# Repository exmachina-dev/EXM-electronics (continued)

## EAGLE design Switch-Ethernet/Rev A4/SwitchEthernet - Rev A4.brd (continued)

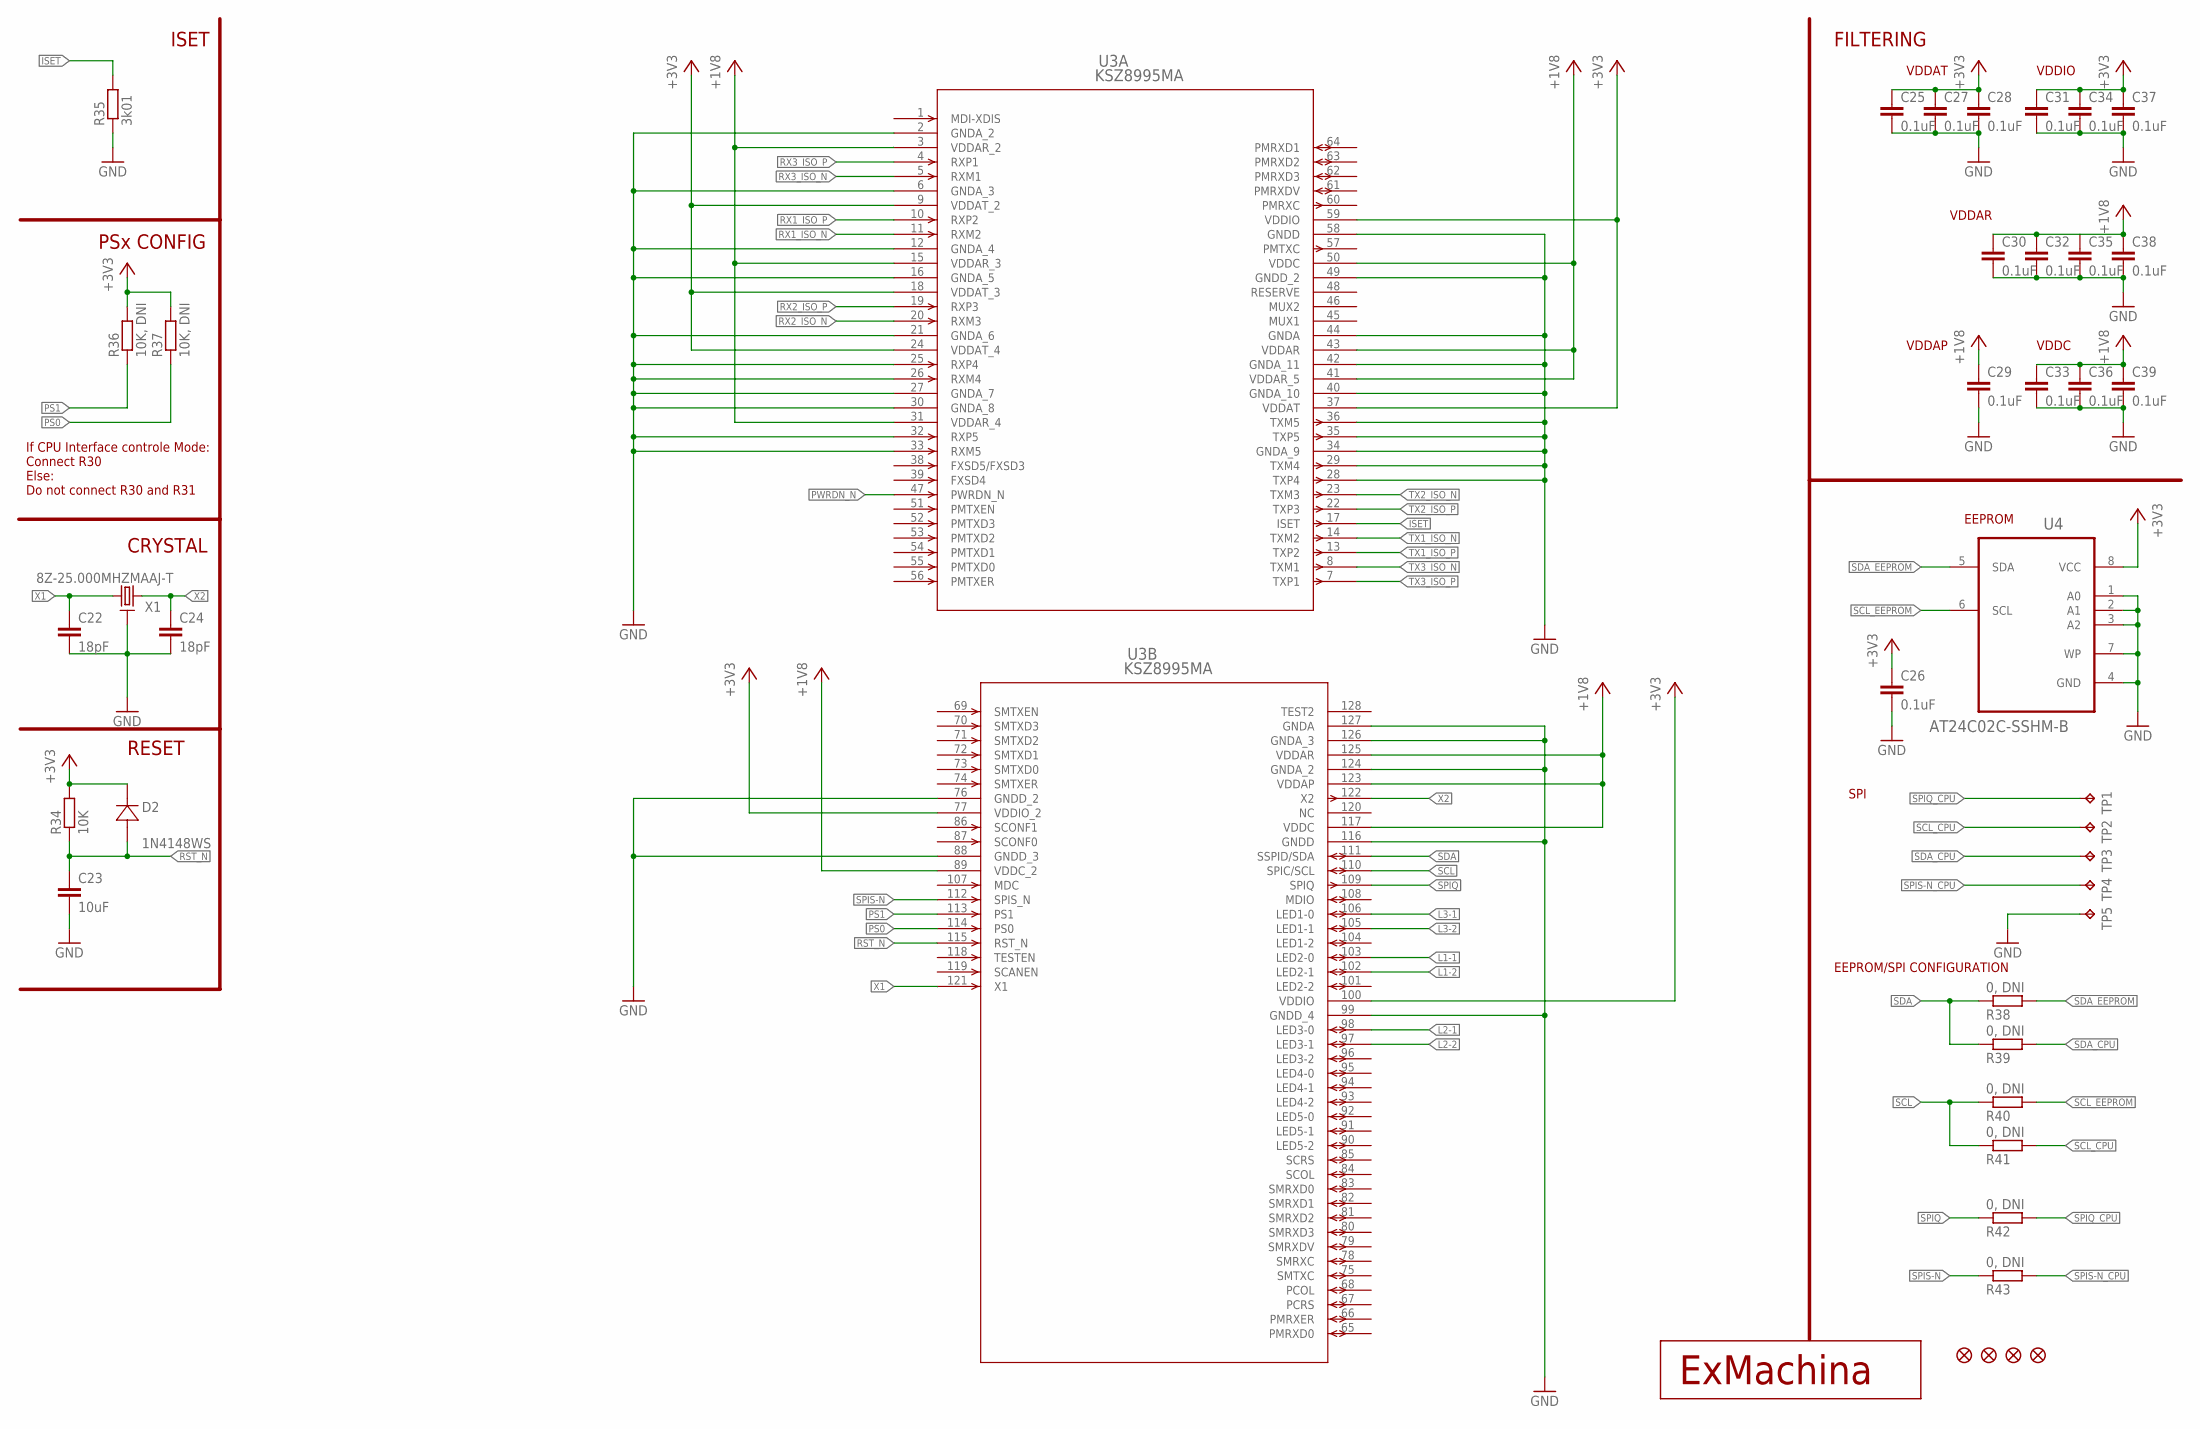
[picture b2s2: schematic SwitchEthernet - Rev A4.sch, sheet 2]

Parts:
C22, C24: 18pF; C0603; MPN MC0603N180J500CT
C23: 10uF; C0603; MPN GRM188R60J106ME47D
C25, C26, C27, C28, C29, C30, C31, C32, C33, C34, C35, C36, C37, C38, C39: 0.1uF; C0603; MPN MC0603B104K160CT
D2: 1N4148WS; SOD323-W; MPN 1N4148WS.
JP1, JP2, JP3, JP4: FIDUCIAL1X2; FIDUCIAL-1X2
R34: 10K; R0603; MPN MC0063W0603110K
R35: 3k01; R0603; MPN MC0063W060313K01
R36, R37: 10K, DNI; R0603; MPN MC0063W0603110K
R38, R39, R40, R41, R42, R43: 0, DNI; R0603; MPN MC0603WG00000T5E-TC
T3: EXMACHINA-LOGO-NAME; EXM-LOGO-BASELINE
TP1, TP2, TP3, TP4, TP5: TPB1,27; B1,27
U3: KSZ8995MA; PQFP-128_MQL
U4: AT24C02C-SSHM-B; SOIC127P600X175-8N
X1: 8Z-25.000MHZMAAJ-T; SMD2.5X2; MPN 8Z-25.000MAAJ-T

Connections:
+1V8: C29.1, C30.1, C32.1, C33.1, C35.1, C36.1, C38.1, C39.1, U3.3 (VDDAR_2), U3.15 (VDDAR_3), U3.31 (VDDAR_4), U3.41 (VDDAR_5), U3.43 (VDDAR), U3.50 (VDDC), U3.89 (VDDC_2), U3.117 (VDDC), U3.123 (VDDAP), U3.125 (VDDAR); also elsewhere on the board
+3V3: C25.1, C26.1, C27.1, C28.1, C31.1, C34.1, C37.1, D2.C (1), R34.2, R36.2, R37.2, U3.9 (VDDAT_2), U3.18 (VDDAT_3), U3.24 (VDDAT_4), U3.37 (VDDAT), U3.59 (VDDIO), U3.77 (VDDIO_2), U3.100 (VDDIO), U4.8 (VCC); also elsewhere on the board
GND: C22.2, C23.2, C24.2, C25.2, C26.2, C27.2, C28.2, C29.2, C30.2, C31.2, C32.2, C33.2, C34.2, C35.2, C36.2, C37.2, C38.2, C39.2, R35.1, TP5.TP, U3.2 (GNDA_2), U3.6 (GNDA_3), U3.12 (GNDA_4), U3.16 (GNDA_5), U3.21 (GNDA_6), U3.25 (RXP4), U3.26 (RXM4), U3.27 (GNDA_7), U3.28 (TXP4), U3.29 (TXM4), U3.30 (GNDA_8), U3.32 (RXP5), U3.33 (RXM5), U3.34 (GNDA_9), U3.35 (TXP5), U3.36 (TXM5), U3.40 (GNDA_10), U3.42 (GNDA_11), U3.44 (GNDA), U3.49 (GNDD_2), U3.58 (GNDD), U3.76 (GNDD_2), U3.88 (GNDD_3), U3.99 (GNDD_4), U3.116 (GNDD), U3.124 (GNDA_2), U3.126 (GNDA_3), U3.127 (GNDA), U4.1 (A0), U4.2 (A1), U4.3 (A2), U4.4 (GND), U4.7 (WP), X1.2, X1.4 (2); also elsewhere on the board
ISET: R35.2, U3.17 (ISET)
L1-1: U3.103 (LED2-0); also elsewhere on the board
L1-2: U3.102 (LED2-1); also elsewhere on the board
L2-1: U3.98 (LED3-0); also elsewhere on the board
L2-2: U3.97 (LED3-1); also elsewhere on the board
L3-1: U3.106 (LED1-0); also elsewhere on the board
L3-2: U3.105 (LED1-1); also elsewhere on the board
PS0: R37.1, U3.114 (PS0)
PS1: R36.1, U3.113 (PS1)
PWRDN_N: U3.47 (PWRDN_N)
RST_N: C23.1, D2.A (2), R34.1, U3.115 (RST_N)
RX1_ISO_N: U3.11 (RXM2); also elsewhere on the board
RX1_ISO_P: U3.10 (RXP2); also elsewhere on the board
RX2_ISO_N: U3.20 (RXM3); also elsewhere on the board
RX2_ISO_P: U3.19 (RXP3); also elsewhere on the board
RX3_ISO_N: U3.5 (RXM1); also elsewhere on the board
RX3_ISO_P: U3.4 (RXP1); also elsewhere on the board
SCL: R40.1, R41.1, U3.110 (SPIC/SCL)
SCL_CPU: R41.2, TP2.TP
SCL_EEPROM: R40.2, U4.6 (SCL)
SDA: R38.1, R39.1, U3.111 (SSPID/SDA)
SDA_CPU: R39.2, TP3.TP
SDA_EEPROM: R38.2, U4.5 (SDA)
SPIQ: R42.1, U3.109 (SPIQ)
SPIQ_CPU: R42.2, TP1.TP
SPIS-N: R43.1, U3.112 (SPIS_N)
SPIS-N_CPU: R43.2, TP4.TP
TX1_ISO_N: U3.14 (TXM2); also elsewhere on the board
TX1_ISO_P: U3.13 (TXP2); also elsewhere on the board
TX2_ISO_N: U3.23 (TXM3); also elsewhere on the board
TX2_ISO_P: U3.22 (TXP3); also elsewhere on the board
TX3_ISO_N: U3.8 (TXM1); also elsewhere on the board
TX3_ISO_P: U3.7 (TXP1); also elsewhere on the board
X1: C22.1, U3.121 (X1), X1.1
X2: C24.1, U3.122 (X2), X1.3

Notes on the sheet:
ISET
FILTERING
VDDIO
VDDAT
VDDAR
VDDC
VDDAP
PSx CONFIG
If CPU Interface controle Mode: Connect R30 Else: Do not connect R30 and R31
CRYSTAL
EEPROM
SPI
EEPROM/SPI CONFIGURATION
RESET

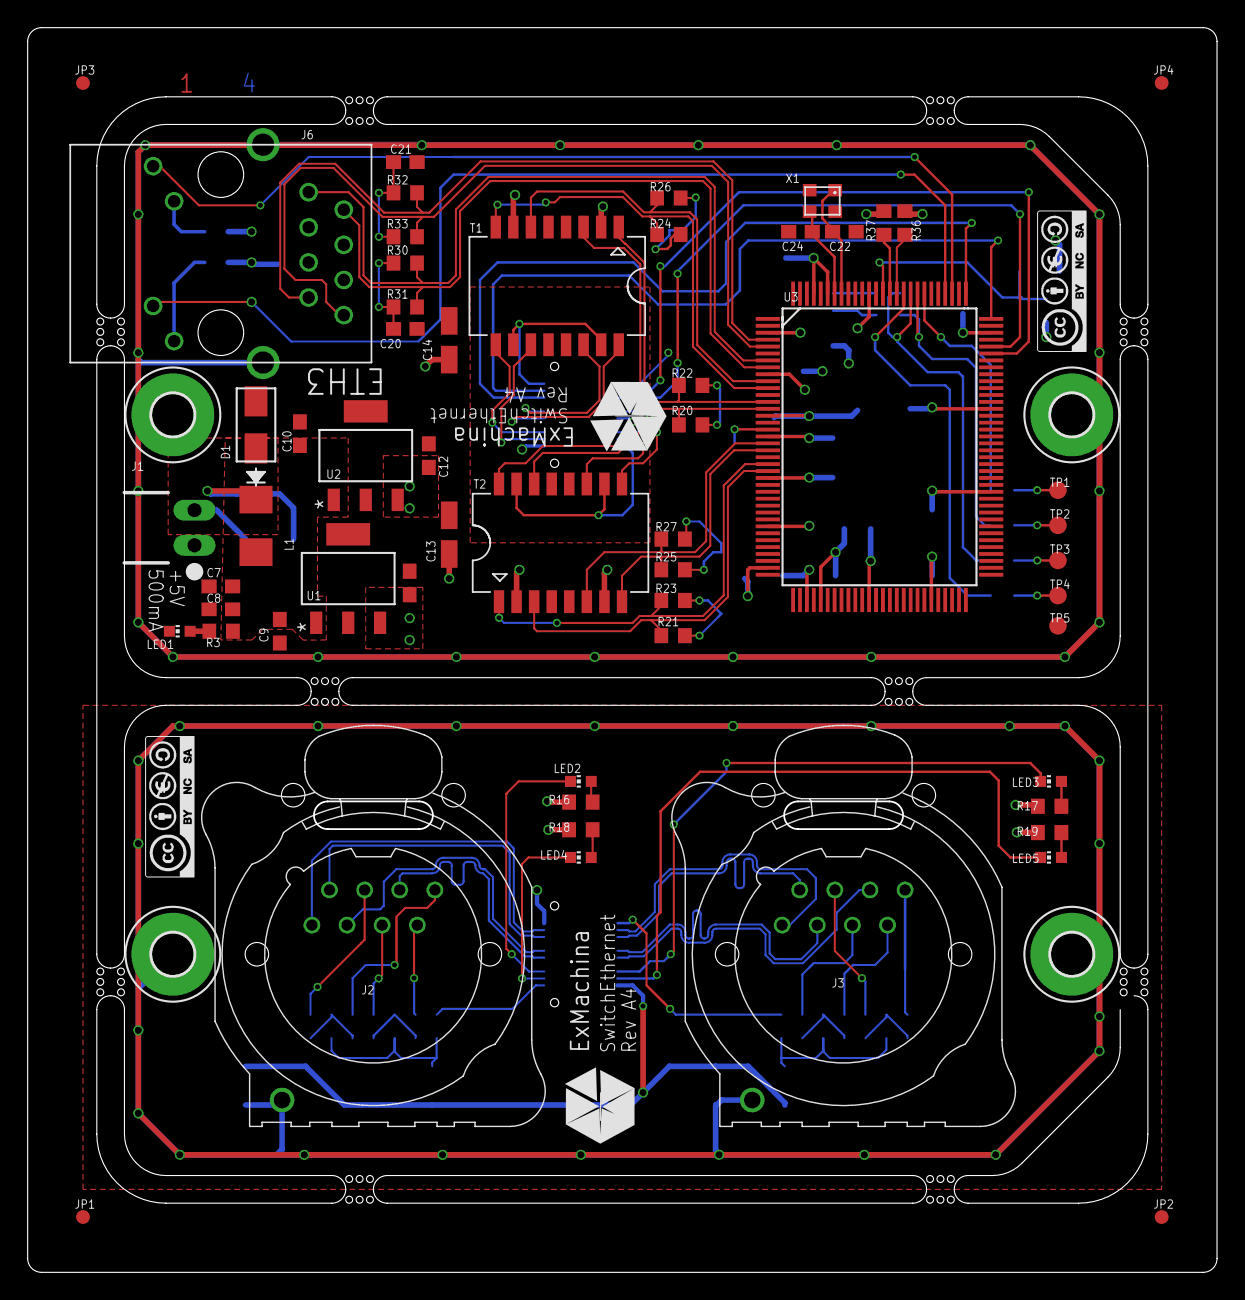
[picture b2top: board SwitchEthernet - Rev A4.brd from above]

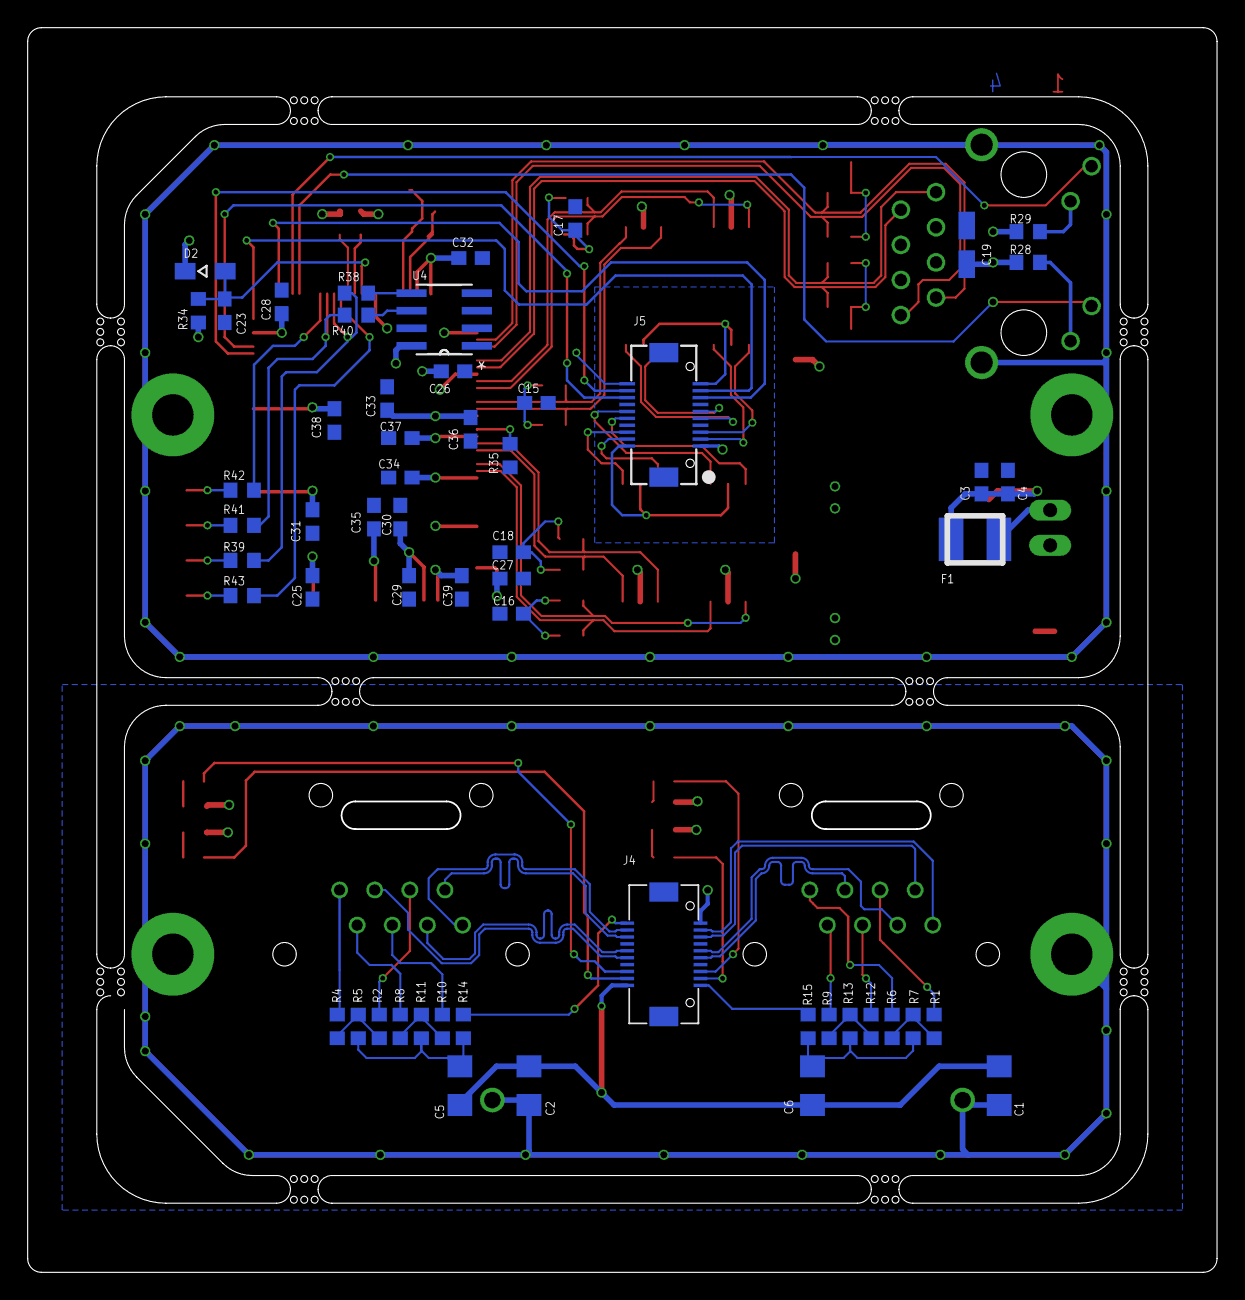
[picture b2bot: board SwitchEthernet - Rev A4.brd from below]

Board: 4 copper layers, 86.0 x 90.0 mm, 122 parts (56 on the bottom side), 78 nets.

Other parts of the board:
U$2, U$3: CC-BY-NC-SA
U$4: EXMACHINA-LOGO-NAME; EXM-LOGO-BASELINE
U$5: A5L-LOC
